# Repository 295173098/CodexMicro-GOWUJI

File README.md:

# GOWUJI Macro Pad

<p align="center"><sub><b>Rev C 工程样机</b> · 带壳 3D 渲染（CAD 渲染，非实物照片）</sub></p>

| **PCB 正面** · 4 层 · 95 × 98 mm | **PCB 背面** · 电源与地平面 |
| :---: | :---: |
|  |  |

> **当前工程候选：Rev C（REVIEW ONLY）**。四层板、直接贴装 ESP32-S3、独立 LED 5 V 阻尼支路；ERC/DRC/一致性 0，板级仿真通过，但**尚未下单、未做实物验证**。源文件在 [hardware/rev-c/](hardware/rev-c/)，验证记录见 [AGENTS.md](AGENTS.md)；Rev B 下单说明见 [docs/rev-b-order.md](docs/rev-b-order.md)。

> **Rev B PCB + 工厂贴装打样**：使用[Rev B 下单说明](docs/rev-b-order.md)和本地 `build/rev-b-pcba.zip`；工厂 CAM/供料/旋转回签后做 3–5 套工程样机。下方 A4 的双层板和成本不能代用。

<details>
<summary>更多 3D 渲染</summary>

| 背面 | 后侧 USB-C | PCB 正上方 |
| :---: | :---: | :---: |
|  |  |  |

</details>

## Rev A4 DIY 基线

按 [OpenAI × Work Louder Codex Micro](https://openai.com/zh-Hans-CN/supply/co-lab/work-louder/) 键位设计的 DIY 控制台。采用 95 × 98 mm 双层 PCB、Waveshare ESP32-S3-Zero-M、13 个直焊 MX 轴（其中两个共用 2U 语音键帽）、六颗独立状态灯、五向摇杆、带按压旋钮和触摸片。外壳、面板、旋钮、导光件和 2U 键帽可打印。当前是 **Alpha 样机设计**，尚未做实物验证。

| 交付 | 文件 |
| --- | --- |
| PCB、原理图、项目库 | [KiCad 项目](hardware/Gowuji-RevA.kicad_pro)、[PCB](hardware/Gowuji-RevA.kicad_pcb)、[原理图](hardware/Gowuji-RevA.kicad_sch) |
| BOM | [BOM.csv](hardware/BOM.csv) |
| 3D 打印 | [底壳](mechanical/base.stl)、[面板](mechanical/plate.stl)、[旋钮](mechanical/dial.stl)、[摇杆帽](mechanical/joystick-cap.stl)、[导光件](mechanical/light-pipes.stl)、[2U 语音键帽](mechanical/ptt-keycap-2u.stl)、[USB 盖](mechanical/usb-cover.stl)、[轴孔试片](mechanical/mx-fit-coupon.stl)、[装配 STEP](mechanical/fit-reference.step) |
| 可选外壳 | [按参考图制作的凹刻圆盘和正面选件](docs/appearance.md) |
| Rev B 布线已闭合，待打样验证 | [直接贴装 ESP32-S3、后置 USB-C 和连续正面](docs/rev-b.md) |
| 固件和烧录 | [Arduino 工程](firmware/Gowuji/)、[烧录脚本](firmware/flash.py) |
| Codex 伴侣 | [Python 主机程序](host/gowuji.py) |
| 制造与验证 | [打样和装配](docs/assembly.md)、[验证记录](docs/validation.md) |

有线模式使用标准 USB HID 键盘；打开伴侣应用并连接 USB 串口后，按键事件改由伴侣处理。按住旋钮再按复位，选择本次开机使用 BLE HID。无线模式需要通过 USB-C 外接 5 V 电源；Rev A 无电池、充电器和无线状态灯同步。普通开机恢复 USB HID。蓝牙配对和 USB 真机枚举尚未验证。

伴侣应用启动独立的 [Codex App Server](https://learn.chatgpt.com/docs/app-server)，不用原厂 VID/PID 或专有协议。它管理自己启动或接入的聊天；不能保证追踪官方桌面应用里正在运行的聊天，也不会出现在原厂设备配置页。旋钮选择下一次发送使用的推理强度，摇杆把提示词填入输入框。A4 的板载数字麦克风通过 USB 传送 16 kHz 单声道 PCM 给伴侣，由本地 Vosk 转写。按住 2U 键采样，松开停止，每次最多 60 秒；系统录音应用和 BLE 模式不提供板载音频。语音和摇杆都只填入草稿，由用户点发送。按键接受/拒绝只对当前会话中已经显示的命令或文件审批有效。

PCB 上六颗灯靠近上方六个磨砂透光状态键，通过面板导光；六个位置映射到伴侣的聊天槽。状态为：无分配熄灭、空闲白、运行蓝、完成绿、待输入黄、错误红。左下触摸片切换六个配置层；底部宽键下两轴合并为一个按住说话事件。传入 `--profiles host/profiles.example.json` 可替换每层的摇杆提示词和部分命令键；标准 HID 模式保持固定键值。

| 位置 | 第 1 列 | 第 2 列 | 第 3 列 | 第 4 列 |
| --- | --- | --- | --- | --- |
| 第 1 排 | 旋钮 | 会话 1 | 会话 2 | 摇杆 |
| 第 2 排 | 会话 3 | 会话 4 | 会话 5 | 会话 6 |
| 第 3 排 | 新聊天 | 接受 | 拒绝 | 中止当前回合 |
| 第 4 排 | 触摸切层 | 按住说话（2U 左） | 同一键（2U 右） | 查找 / 分配 |

成本估算约 **¥63–170 / 套**，含小批量摊销裸 PCB 和自打耗材，不含人工、运费、代贴和外置电源。板载麦克风、阻容和密封圈约增加 ¥3–10。六个状态位用磨砂透光 1U MX 键帽，其余单宽命令键可复用通用键帽。量产前必须完成 [USB 与整机首件验证](docs/validation.md)。

本地编译和启动：

```powershell
python tools/build_firmware.py --install
python -m pip install esptool==5.1.0
python firmware/flash.py COM6 GOWUJI-v0.1.0-alpha.4-flash-0x0.bin
python -m pip install -r host/requirements.txt
python host/gowuji.py --port COM6 --cwd C:/path/to/project
```

上面用的是 Windows 示例端口；macOS/Linux 替换成对应串口路径。无需硬件可用 `python host/gowuji.py --demo` 查看灯状态。语音可选装 `host/requirements-voice.txt`，下载匹配语言的 [Vosk 模型](https://alphacephei.com/vosk/models)，并启动时增加 `--voice-model <模型目录>`。若使用 A3 或希望改用电脑麦克风，另装 `sounddevice`，并增加 `--mic computer`。

硬件使用 KiCad 9 打开。修改源数据后可用 `python tools/hardware.py` 更新原理图、BOM、项目库及固件引脚；该命令不会覆写已布线 PCB。若重新布局，`--unrouted build/layout.kicad_pcb` 生成裸布局，再在 KiCad 中布线并另存。用 `python mechanical/generate.py`（CadQuery 2.8）重建机械文件。用 `python tools/export_hardware.py` 重跑检查和制造导出。Release 同时提供可烧录的完整镜像、源码和 Gerber，发布状态见 [AGENTS.md](AGENTS.md)。

在 PCB 编辑器按 `Alt+3` 查看装有器件的板。`hardware/models/` 内含简化的按键、模块、旋钮、摇杆和麦克风 STEP，可用 `python mechanical/kicad_models.py` 重建。`python tools/export_hardware.py --render` 额外生成电路板和带外壳两张 KiCad 渲染图。A4 延用 A3 对齐原厂的键位及按键分区，采用通用 MX 轴、打印外壳和独立伴侣程序；命令默认映射、手感、材料及灯光效果与原厂可能不同。

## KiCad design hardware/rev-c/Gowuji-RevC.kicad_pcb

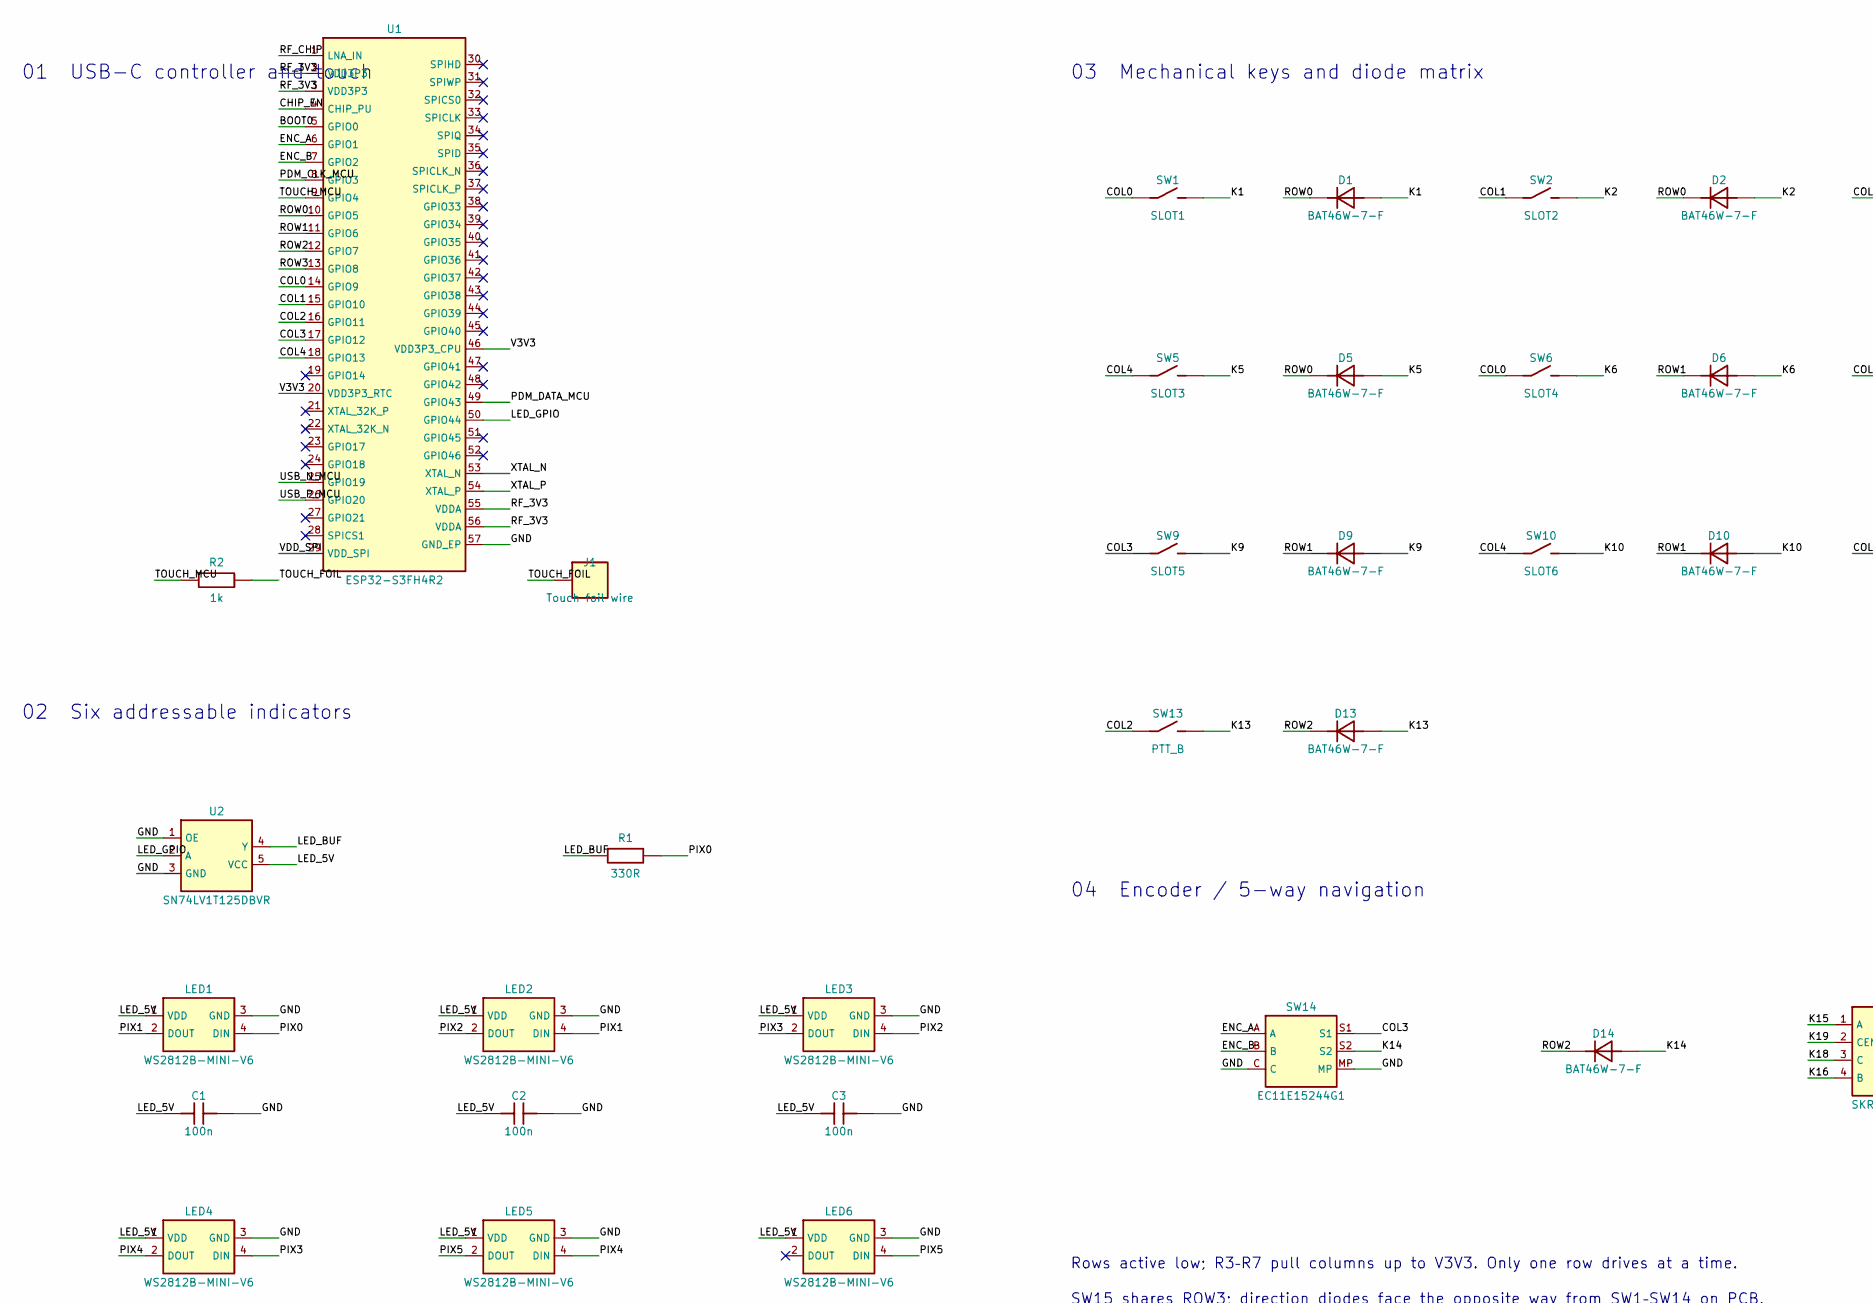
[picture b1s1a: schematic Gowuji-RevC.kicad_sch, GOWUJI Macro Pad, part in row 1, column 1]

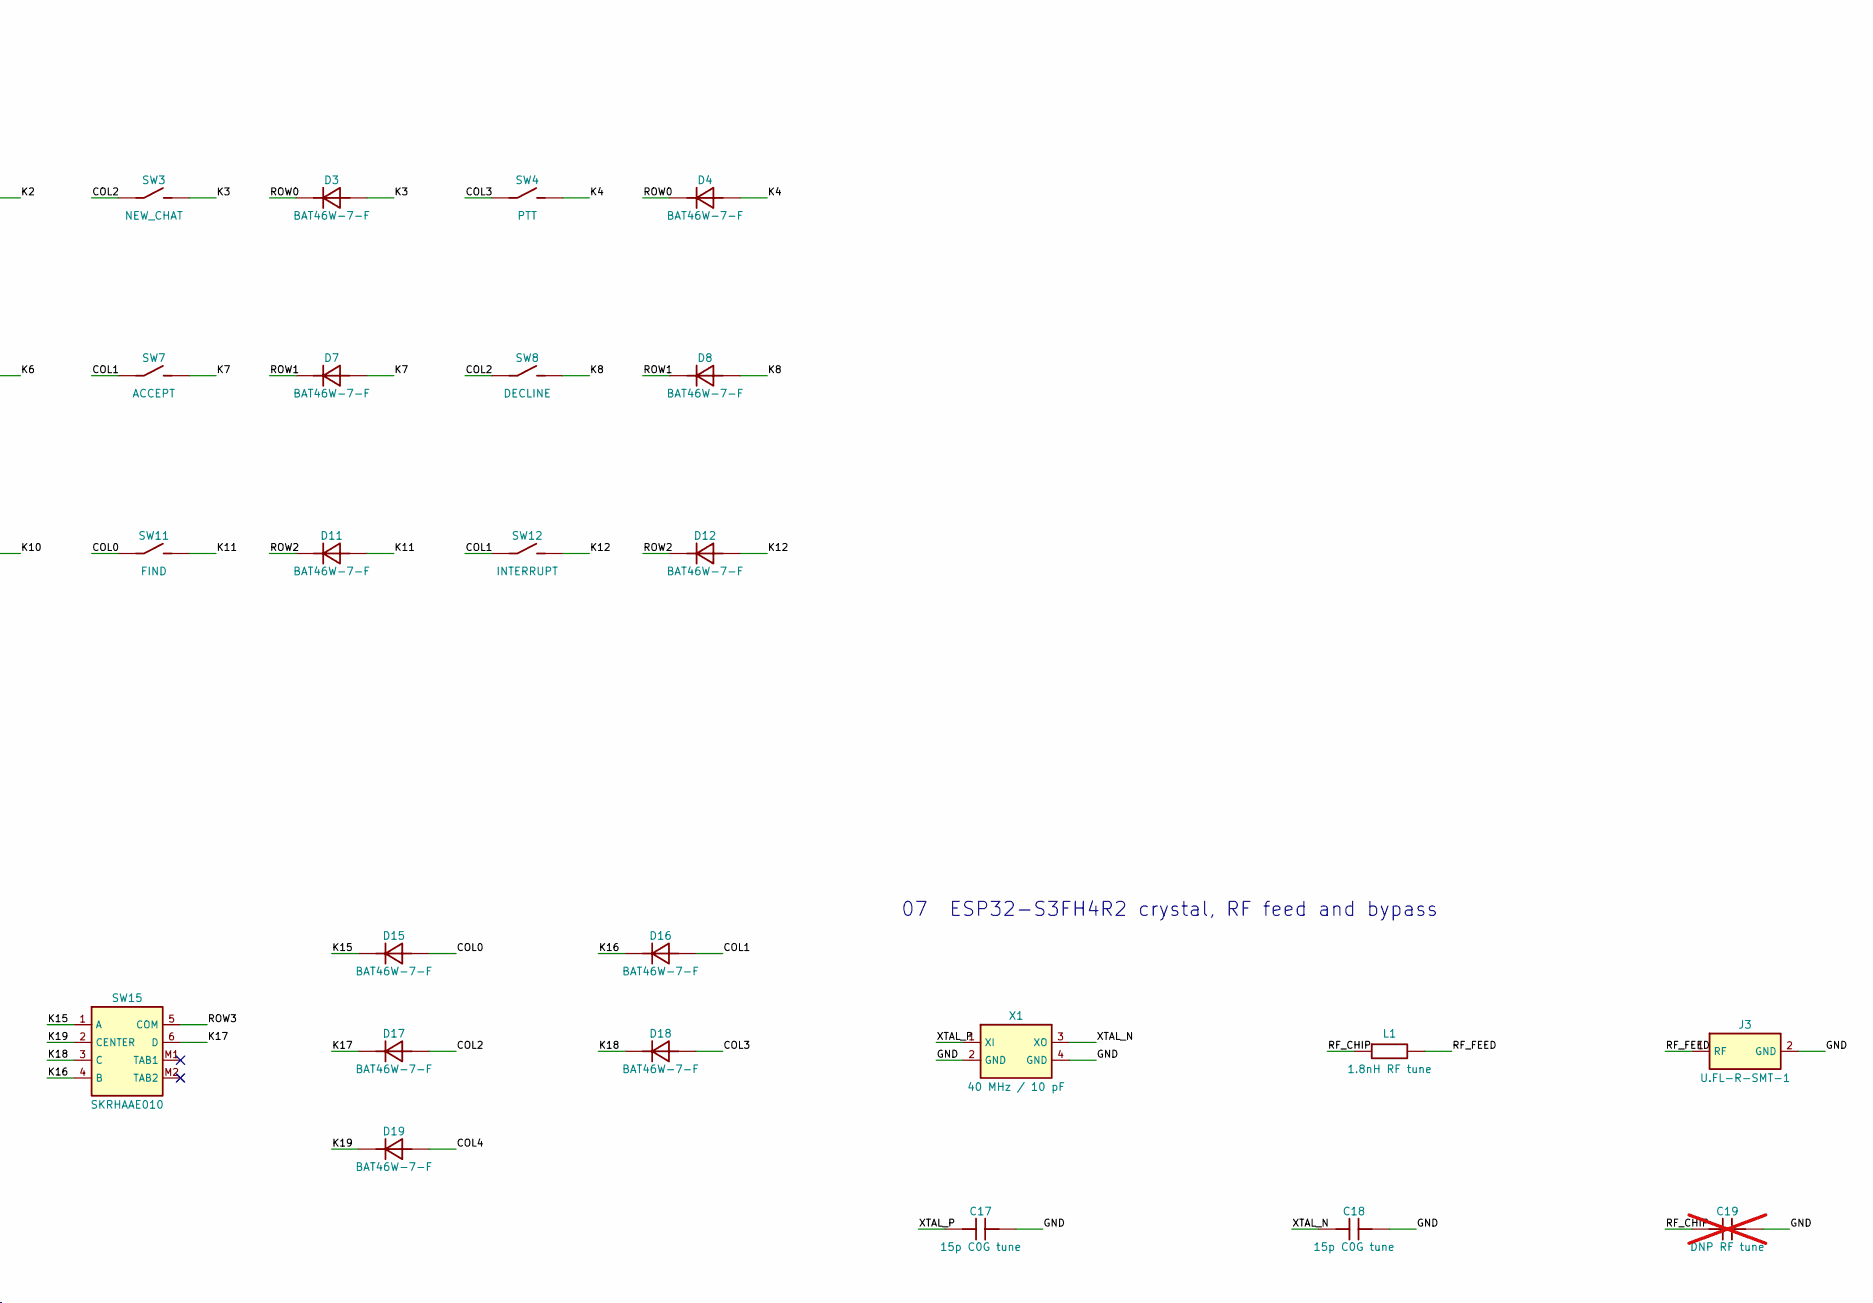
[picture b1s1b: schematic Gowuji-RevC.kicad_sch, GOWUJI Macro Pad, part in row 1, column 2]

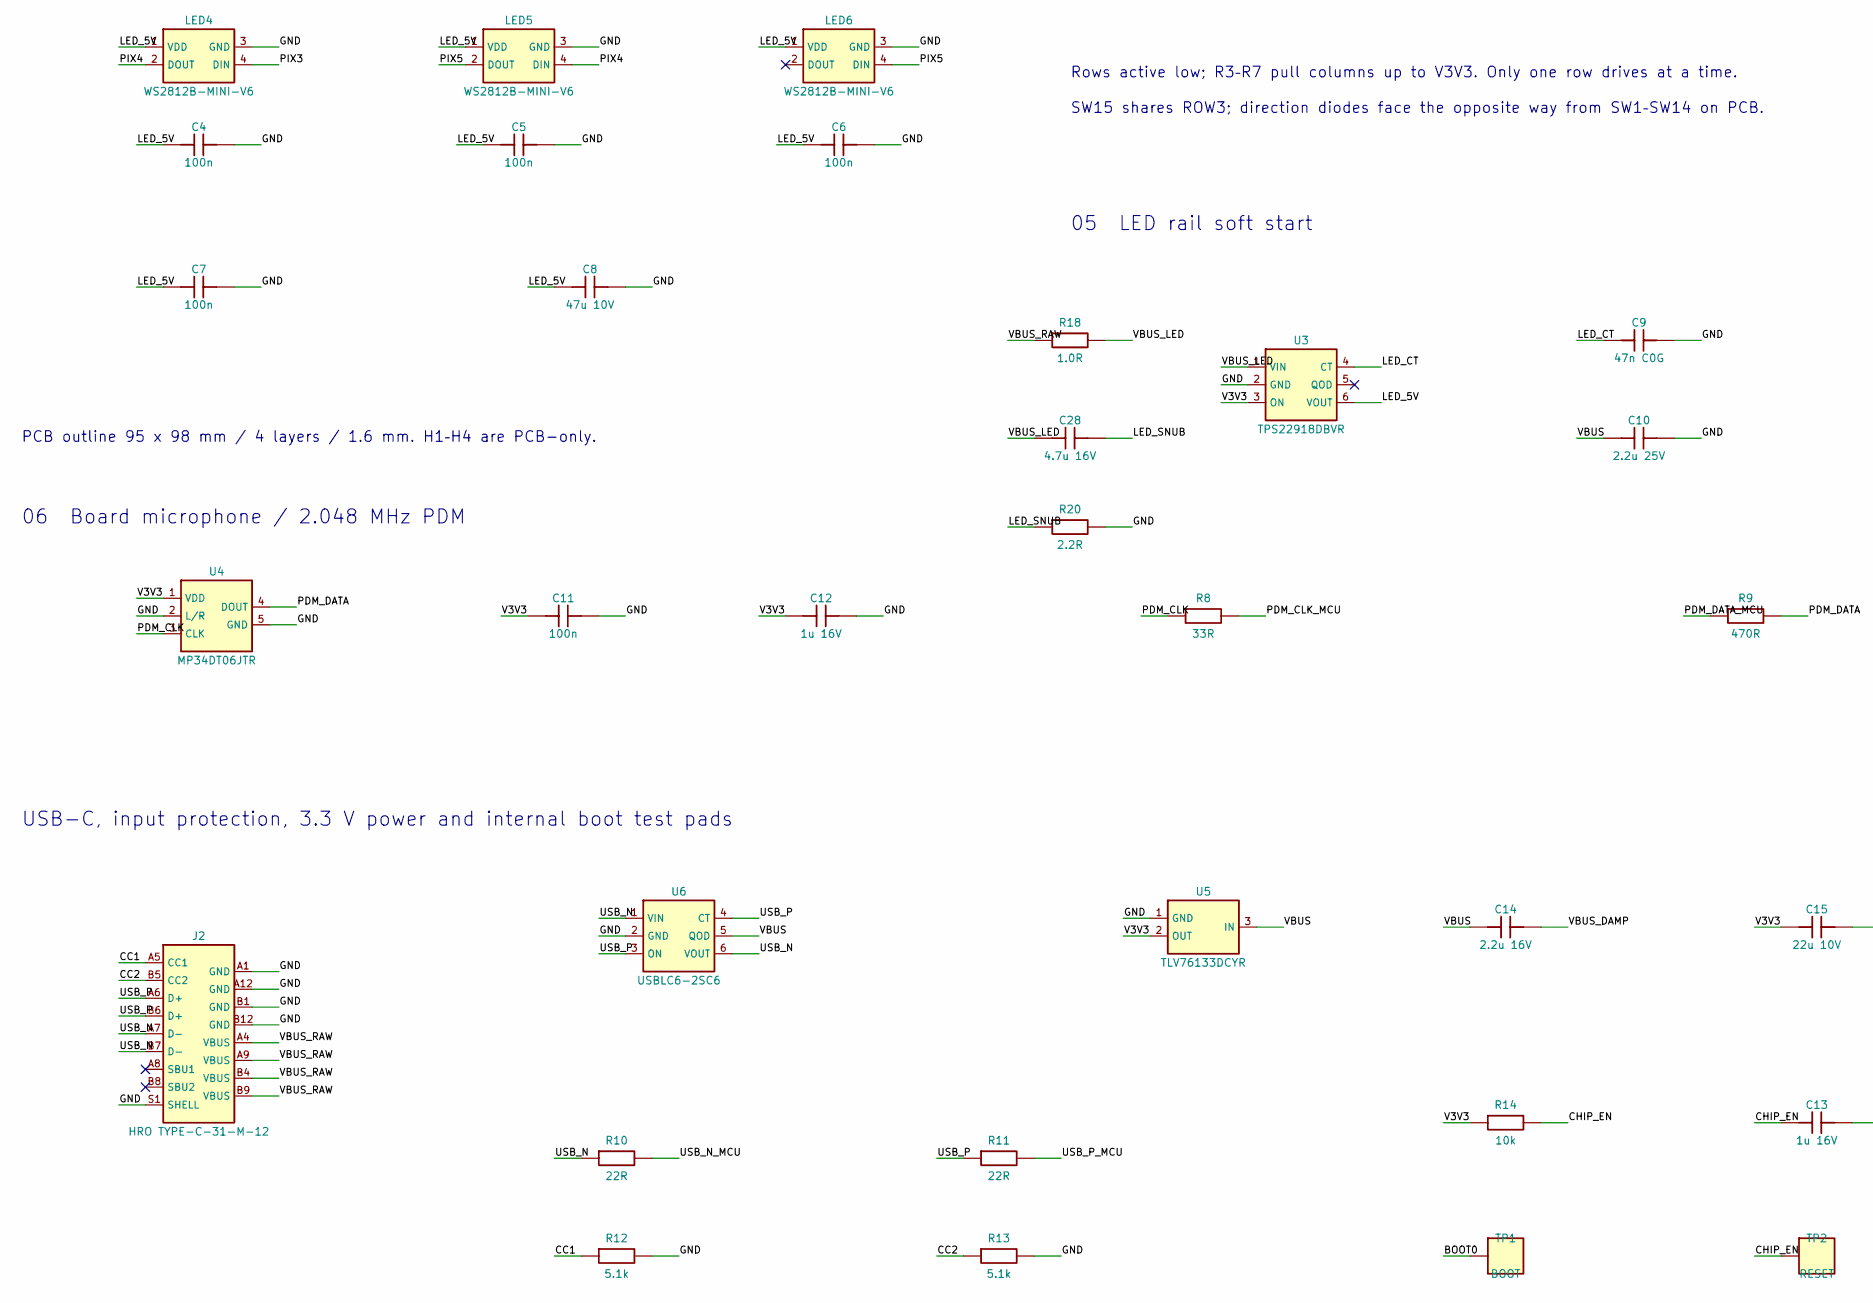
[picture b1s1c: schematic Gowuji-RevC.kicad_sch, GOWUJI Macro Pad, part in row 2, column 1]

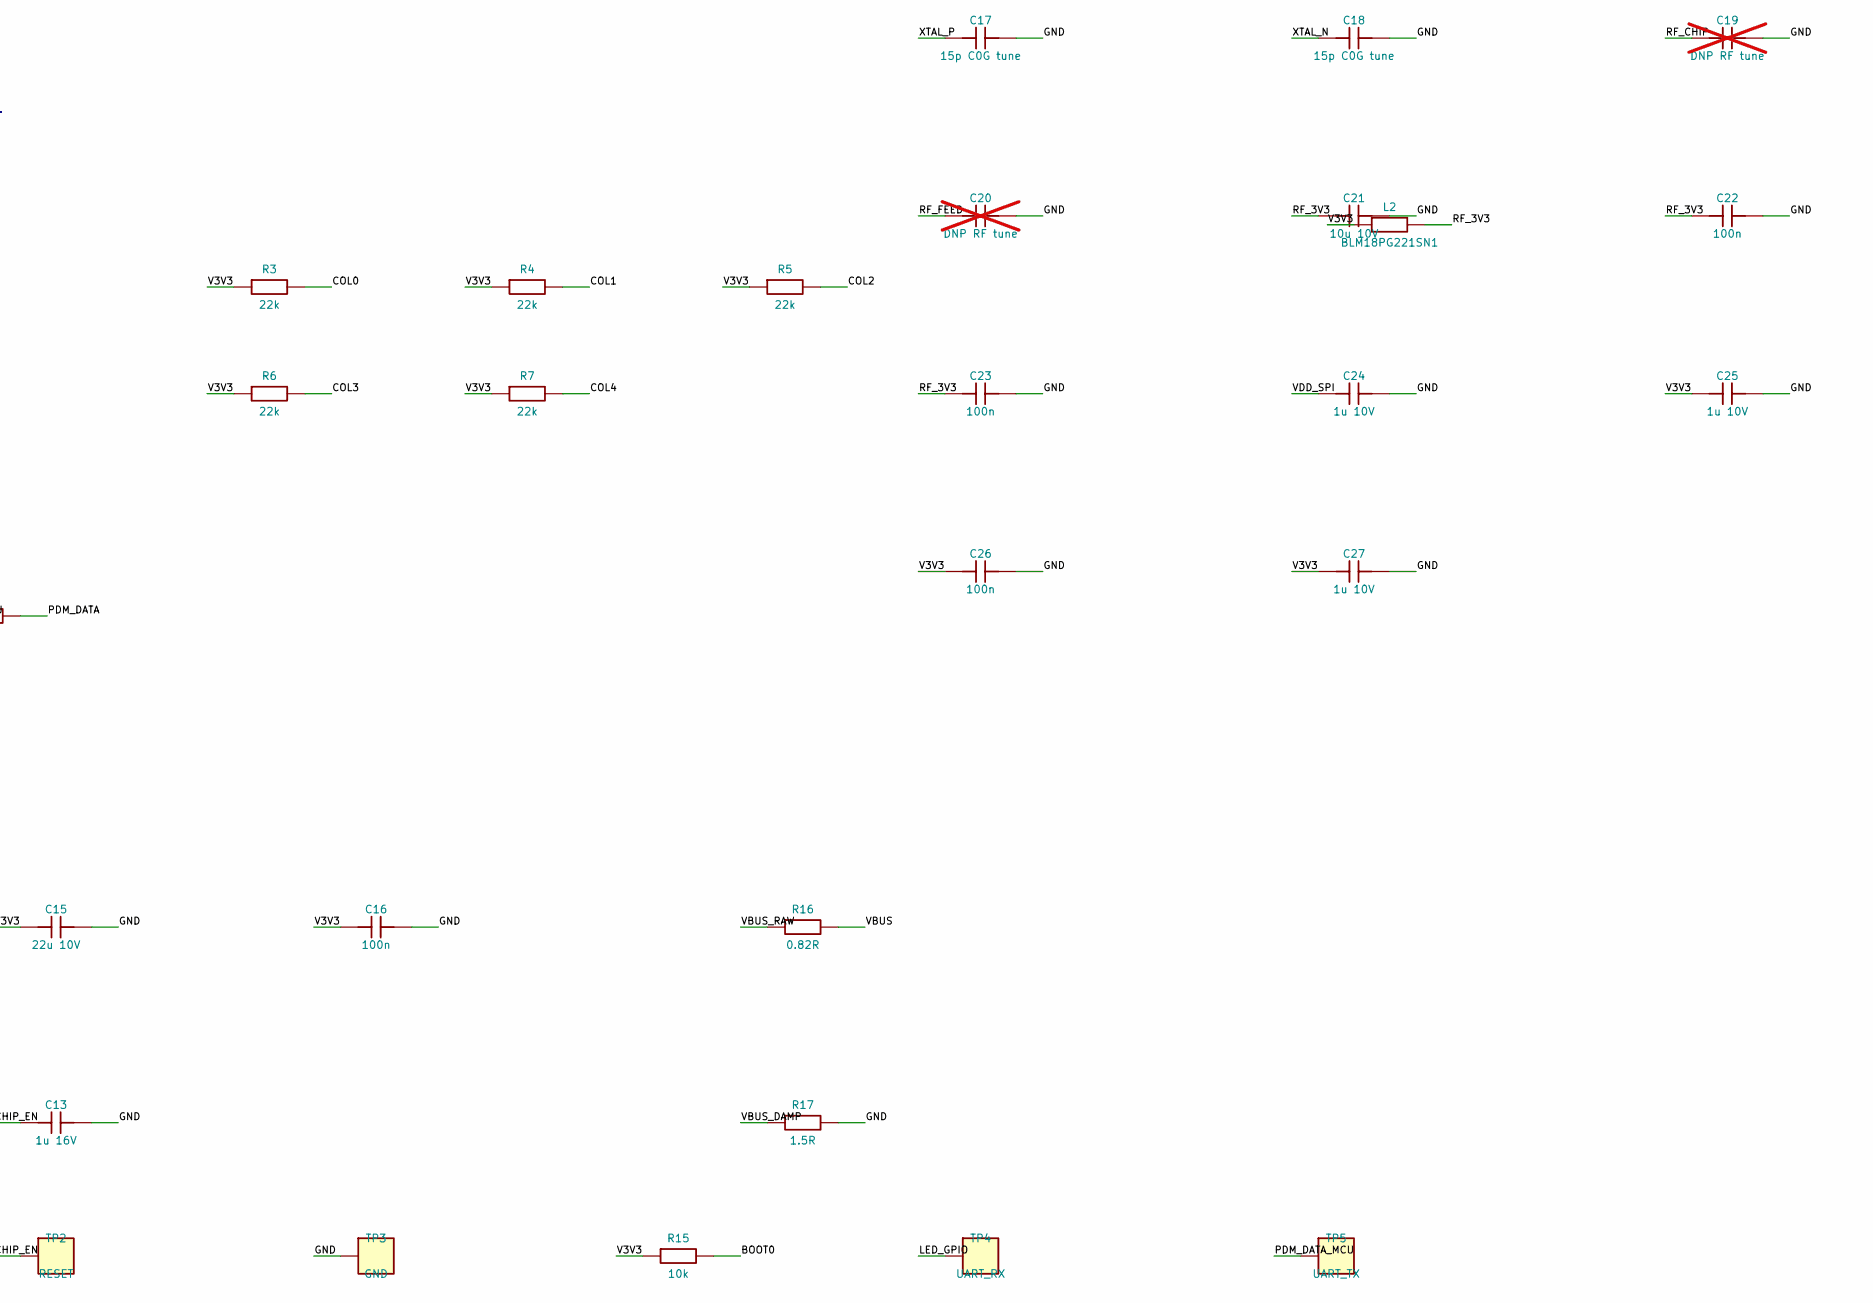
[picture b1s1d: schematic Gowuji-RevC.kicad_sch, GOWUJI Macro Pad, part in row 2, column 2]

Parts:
C1, C2, C3, C4, C5, C6, C7, C11, C16, C22, C23, C26: 100n; C0603
C8: 47u 10V; C1206
C9: 47n C0G; C0603
C10: 2.2u 25V; C0603
C12, C13: 1u 16V; C0603
C14: 2.2u 16V; C1206
C15: 22u 10V; C1206
C17, C18: 15p C0G tune; C0603
C19, C20: DNP RF tune; C0603; not fitted
C21: 10u 10V; C0603
C24, C25, C27: 1u 10V; C0603
C28: 4.7u 16V; C1206
D1, D2, D3, D4, D5, D6, D7, D8, D9, D10, D11, D12, D13, D14, D15, D16, D17, D18, D19: BAT46W-7-F; SOD123
J1: Touch foil wire; Wire
J2: HRO TYPE-C-31-M-12; USB_C
J3: U.FL-R-SMT-1; U.FL_Hirose_U.FL-R-SMT-1_Vertical
L1: 1.8nH RF tune; R0603
L2: BLM18PG221SN1; R0603
LED1, LED2, LED3, LED4, LED5, LED6: WS2812B-MINI-V6; RGB3535
R1: 330R; R0603
R2: 1k; R0603
R3, R4, R5, R6, R7: 22k; R0603
R8: 33R; R0603
R9: 470R; R0603
R10, R11: 22R; R0603
R12, R13: 5.1k; R0603
R14, R15: 10k; R0603
R16: 0.82R; R_1206_3216Metric
R17: 1.5R; R0603
R18: 1.0R; R_1206_3216Metric
R20: 2.2R; R_1206_3216Metric
SW1: SLOT1; MX
SW2: SLOT2; MX
SW3: NEW_CHAT; MX
SW4: PTT; MX
SW5: SLOT3; MX
SW6: SLOT4; MX
SW7: ACCEPT; MX
SW8: DECLINE; MX
SW9: SLOT5; MX
SW10: SLOT6; MX
SW11: FIND; MX
SW12: INTERRUPT; MX
SW13: PTT_B; MX
SW14: EC11E15244G1; EC11
SW15: SKRHAAE010; SKRH
TP1: BOOT; Probe
TP2: RESET; Probe
TP3: GND; Probe
TP4: UART_RX; Probe
TP5: UART_TX; Probe
U1: ESP32-S3FH4R2; S3
U2: SN74LV1T125DBVR; SOT23_5
U3: TPS22918DBVR; SOT23_6
U4: MP34DT06JTR; MP34DT06J
U5: TLV76133DCYR; LDO
U6: USBLC6-2SC6; SOT23_6
X1: 40 MHz / 10 pF; Crystal_SMD_3225-4Pin_3.2x2.5mm

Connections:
/BOOT0: R15.2, TP1.1, U1.5 (GPIO0)
/CC1: J2.A5 (CC1), R12.1
/CC2: J2.B5 (CC2), R13.1
/CHIP_EN: C13.1, R14.2, TP2.1, U1.4 (CHIP_PU)
/COL0: D15.2 (A), R3.2, SW1.1, SW6.1, SW11.1, U1.14 (GPIO9)
/COL1: D16.2 (A), R4.2, SW2.1, SW7.1, SW12.1, U1.15 (GPIO10)
/COL2: D17.2 (A), R5.2, SW3.1, SW8.1, SW13.1, U1.16 (GPIO11)
/COL3: D18.2 (A), R6.2, SW4.1, SW9.1, SW14.S1, U1.17 (GPIO12)
/COL4: D19.2 (A), R7.2, SW5.1, SW10.1, U1.18 (GPIO13)
/ENC_A: SW14.A, U1.6 (GPIO1)
/ENC_B: SW14.B, U1.7 (GPIO2)
/GND: C1.2, C2.2, C3.2, C4.2, C5.2, C6.2, C7.2, C8.2, C9.2, C10.2, C11.2, C12.2, C13.2, C15.2, C16.2, C17.2, C18.2, C19.2, C20.2, C21.2, C22.2, C23.2, C24.2, C25.2, C26.2, C27.2, J2.A1 (GND), J2.A12 (GND), J2.B1 (GND), J2.B12 (GND), J2.S1 (SHELL), J3.2 (GND), LED1.3 (GND), LED2.3 (GND), LED3.3 (GND), LED4.3 (GND), LED5.3 (GND), LED6.3 (GND), R12.2, R13.2, R17.2, R20.2, SW14.C, SW14.MP, TP3.1, U1.57 (GND_EP), U2.1 (OE), U2.3 (GND), U3.2 (GND), U4.2 (L/R), U4.5 (GND), U5.1 (GND), U6.2 (GND), X1.2 (GND), X1.4 (GND)
/K1: D1.2 (A), SW1.2
/K2: D2.2 (A), SW2.2
/K3: D3.2 (A), SW3.2
/K4: D4.2 (A), SW4.2
/K5: D5.2 (A), SW5.2
/K6: D6.2 (A), SW6.2
/K7: D7.2 (A), SW7.2
/K8: D8.2 (A), SW8.2
/K9: D9.2 (A), SW9.2
/K10: D10.2 (A), SW10.2
/K11: D11.2 (A), SW11.2
/K12: D12.2 (A), SW12.2
/K13: D13.2 (A), SW13.2
/K14: D14.2 (A), SW14.S2
/K15: D15.1 (K), SW15.1 (A)
/K16: D16.1 (K), SW15.4 (B)
/K17: D17.1 (K), SW15.6 (D)
/K18: D18.1 (K), SW15.3 (C)
/K19: D19.1 (K), SW15.2 (CENTER)
/LED_5V: C1.1, C2.1, C3.1, C4.1, C5.1, C6.1, C7.1, C8.1, LED1.1 (VDD), LED2.1 (VDD), LED3.1 (VDD), LED4.1 (VDD), LED5.1 (VDD), LED6.1 (VDD), U2.5 (VCC), U3.6 (VOUT)
/LED_BUF: R1.1, U2.4 (Y)
/LED_CT: C9.1, U3.4 (CT)
/LED_GPIO: TP4.1, U1.50 (GPIO44), U2.2 (A)
/LED_SNUB: C28.2, R20.1
/PDM_CLK: R8.1, U4.3 (CLK)
/PDM_CLK_MCU: R8.2, U1.8 (GPIO3)
/PDM_DATA: R9.2, U4.4 (DOUT)
/PDM_DATA_MCU: R9.1, TP5.1, U1.49 (GPIO43)
/PIX0: LED1.4 (DIN), R1.2
/PIX1: LED1.2 (DOUT), LED2.4 (DIN)
/PIX2: LED2.2 (DOUT), LED3.4 (DIN)
/PIX3: LED3.2 (DOUT), LED4.4 (DIN)
/PIX4: LED4.2 (DOUT), LED5.4 (DIN)
/PIX5: LED5.2 (DOUT), LED6.4 (DIN)
/RF_3V3: C21.1, C22.1, C23.1, L2.2, U1.2 (VDD3P3), U1.3 (VDD3P3), U1.55 (VDDA), U1.56 (VDDA)
/RF_CHIP: C19.1, L1.1, U1.1 (LNA_IN)
/RF_FEED: C20.1, J3.1 (RF), L1.2
/ROW0: D1.1 (K), D2.1 (K), D3.1 (K), D4.1 (K), D5.1 (K), U1.10 (GPIO5)
/ROW1: D6.1 (K), D7.1 (K), D8.1 (K), D9.1 (K), D10.1 (K), U1.11 (GPIO6)
/ROW2: D11.1 (K), D12.1 (K), D13.1 (K), D14.1 (K), U1.12 (GPIO7)
/ROW3: SW15.5 (COM), U1.13 (GPIO8)
/TOUCH_FOIL: J1.1, R2.2
/TOUCH_MCU: R2.1, U1.9 (GPIO4)
/USB_N: J2.A7 (D-), J2.B7 (D-), R10.1, U6.1 (VIN), U6.6 (VOUT)
/USB_N_MCU: R10.2, U1.25 (GPIO19)
/USB_P: J2.A6 (D+), J2.B6 (D+), R11.1, U6.3 (ON), U6.4 (CT)
/USB_P_MCU: R11.2, U1.26 (GPIO20)
/V3V3: C11.1, C12.1, C15.1, C16.1, C25.1, C26.1, C27.1, L2.1, R3.1, R4.1, R5.1, R6.1, R7.1, R14.1, R15.1, U1.20 (VDD3P3_RTC), U1.46 (VDD3P3_CPU), U3.3 (ON), U4.1 (VDD), U5.2 (OUT)
/VBUS: C10.1, C14.1, R16.2, U5.3 (IN), U6.5 (QOD)
/VBUS_DAMP: C14.2, R17.1
/VBUS_LED: C28.1, R18.2, U3.1 (VIN)
/VBUS_RAW: J2.A4 (VBUS), J2.A9 (VBUS), J2.B4 (VBUS), J2.B9 (VBUS), R16.1, R18.1
/VDD_SPI: C24.1, U1.29 (VDD_SPI)
/XTAL_N: C18.1, U1.53 (XTAL_N), X1.3 (XO)
/XTAL_P: C17.1, U1.54 (XTAL_P), X1.1 (XI)

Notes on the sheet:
01 USB-C controller and touch
02 Six addressable indicators
05 LED rail soft start
03 Mechanical keys and diode matrix
04 Encoder / 5-way navigation
Rows active low; R3–R7 pull columns up to V3V3. Only one row drives at a time.
USB-C, input protection, 3.3 V power and internal boot test pads
07 ESP32-S3FH4R2 crystal, RF feed and bypass
SW15 shares ROW3; direction diodes face the opposite way from SW1–SW14 on PCB.
PCB outline 95 x 98 mm / 4 layers / 1.6 mm. H1–H4 are PCB-only.
06 Board microphone / 2.048 MHz PDM

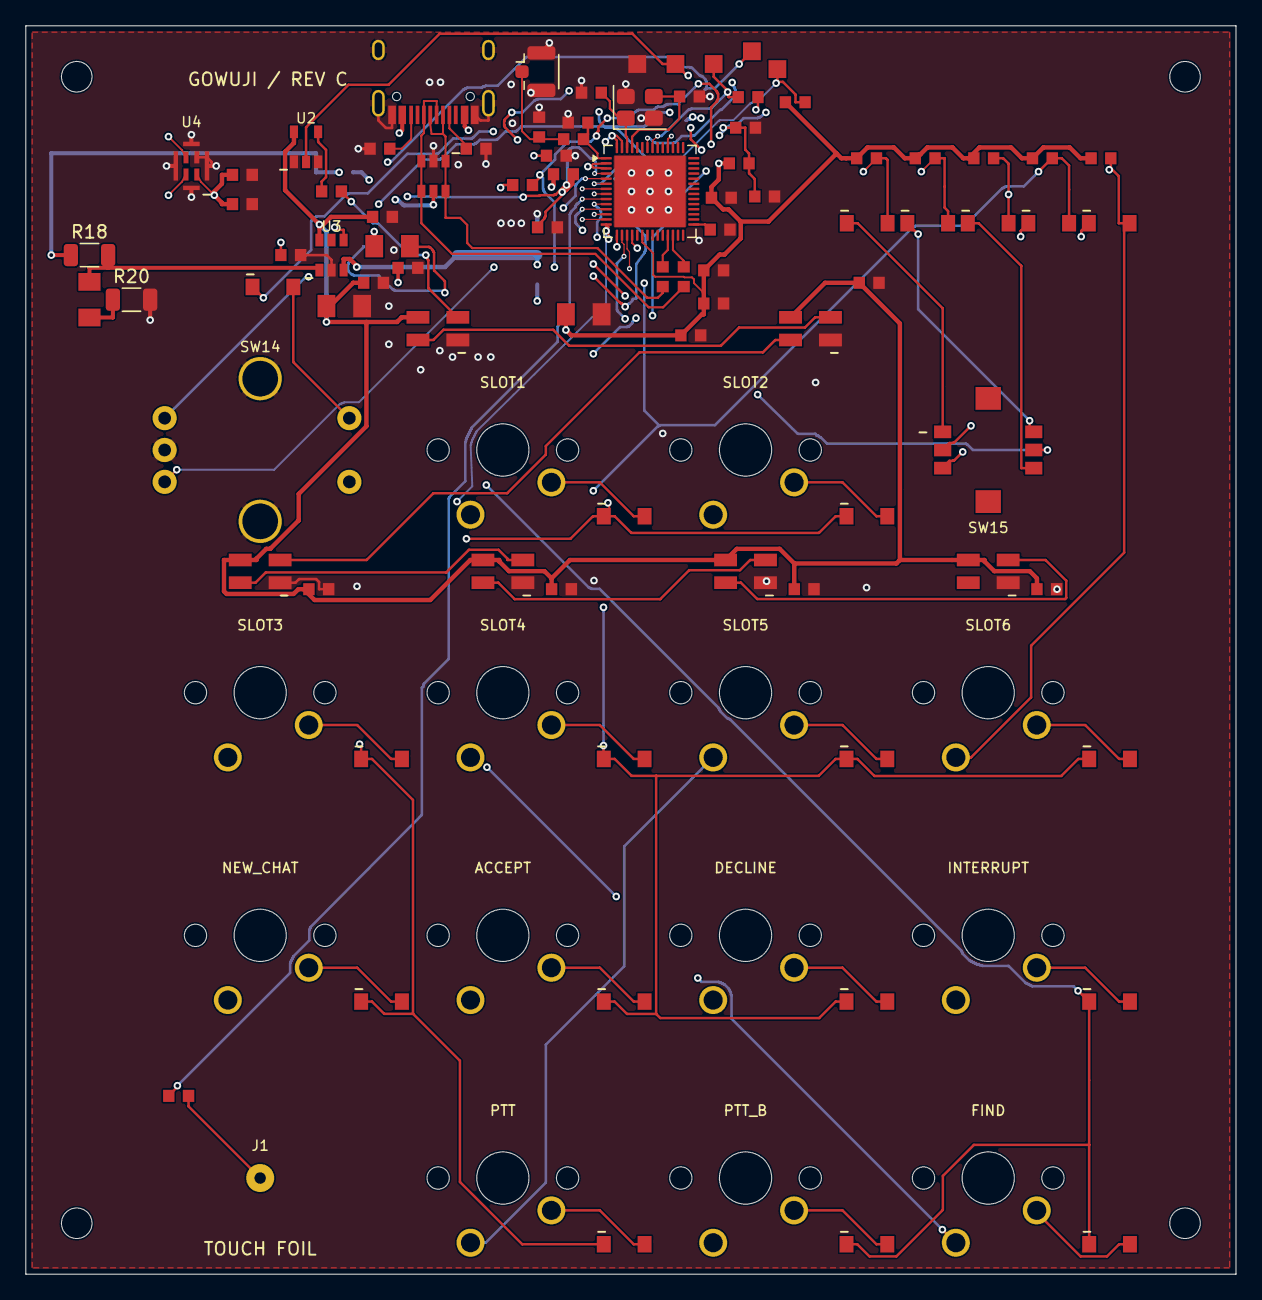
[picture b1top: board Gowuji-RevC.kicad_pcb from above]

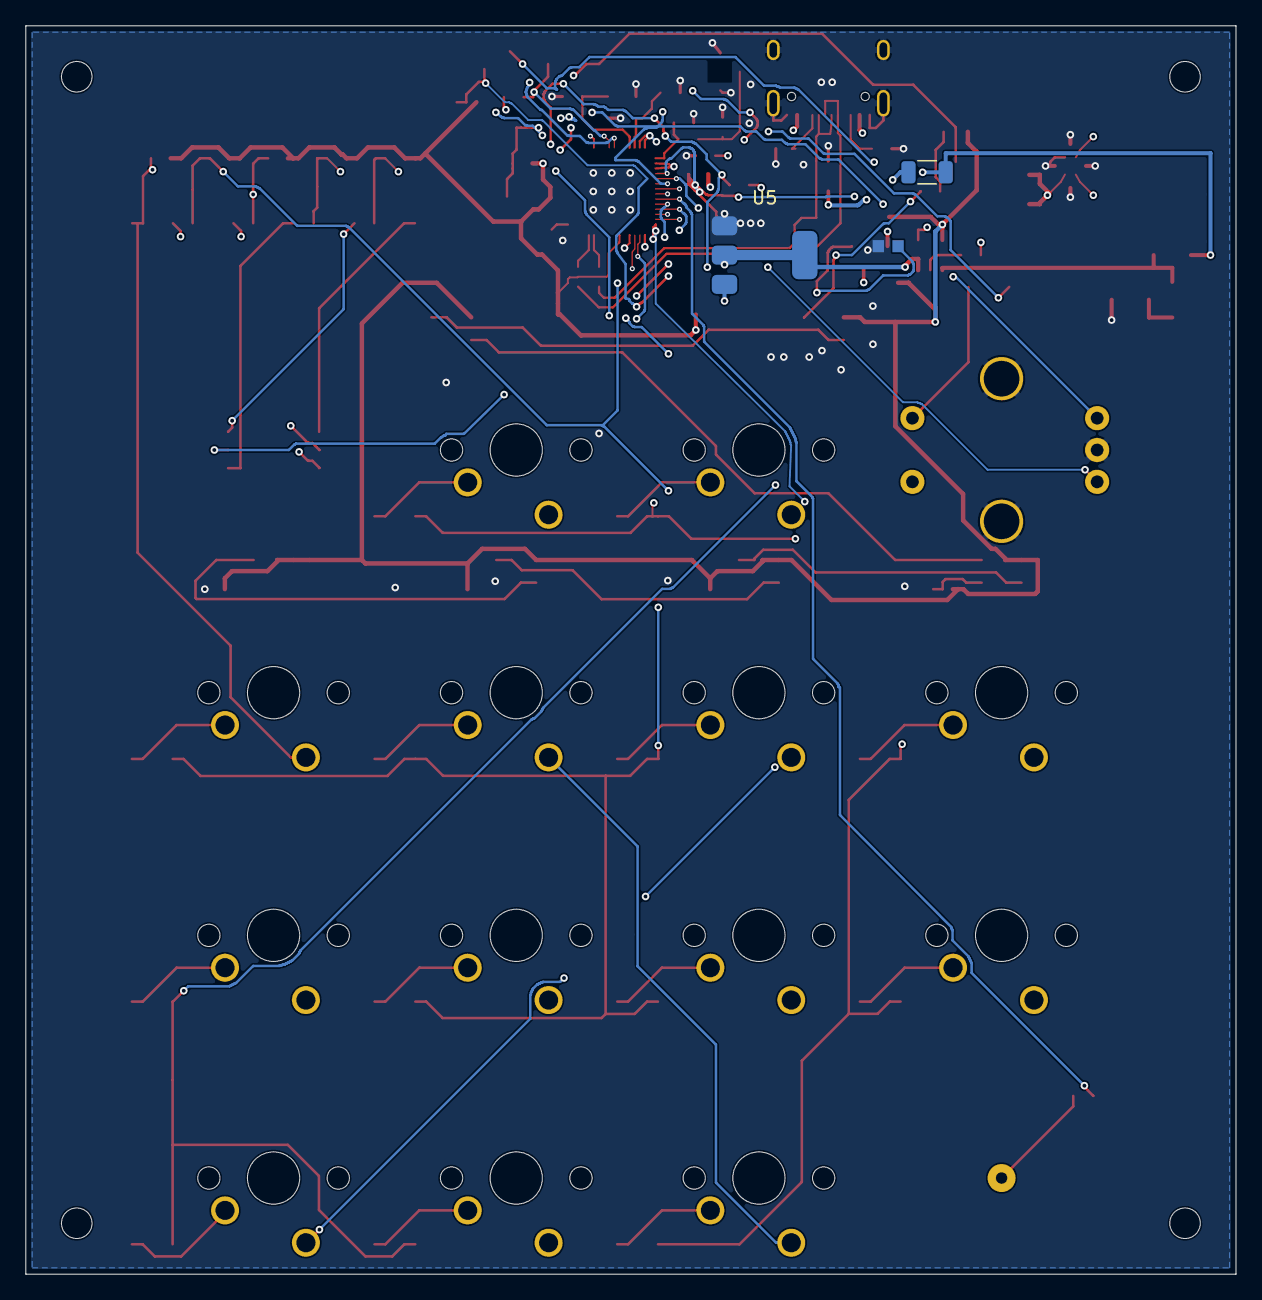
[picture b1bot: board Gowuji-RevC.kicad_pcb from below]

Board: 4 copper layers, 95.0 x 98.0 mm, 108 parts (3 on the bottom side), 67 nets.

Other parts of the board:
H1, H2, H3, H4: M2; Mount

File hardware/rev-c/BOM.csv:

Refs,Qty,Part,Notes,CNY low,CNY high
U2,1,TI SN74LV1T125DBVR,SOT-23-5; 1.8–5.5 V translator,0.7,2.5
U3,1,TI TPS22918DBVR,SOT-23-6; 5 V LED rail load switch,1.5,5
SW1-SW13,13,MX-compatible 3-pin or 5-pin switches,solder type; match SW4 and SW13 for the shared 2U cap,0.65,1.5
SW14,1,ALPS EC11E15244G1,push encoder; confirm drawing / D shaft,5,12
SW15,1,ALPS SKRHAAE010,no guide bosses; verify footprint before substituting,5,16
D1-D19,19,Diodes Inc. BAT46W-7-F,SOD-123; low forward drop Schottky,0.08,0.3
LED1-LED6,6,Worldsemi WS2812B-MINI-V6,3535; verify MINI-V6 (no X1 suffix),0.3,0.9
R1,1,330 ohm,0603,0.02,0.1
R2,1,1 kohm,0603,0.02,0.1
R3-R7,5,22 kohm ±1%,0603; matrix column pull-ups,0.02,0.1
C1-C7,7,100 nF X7R 16 V,0603,0.04,0.12
C8,1,47 uF X5R 10 V,1206; ceramic,0.3,1
C9,1,47 nF C0G 50 V,0603; load-switch slew-rate capacitor; ~129 ms 10-90% at 5 V,0.06,0.25
U4,1,ST MP34DT06JTR,C503097; top-port PDM; no wash or coating over inlet,3,9
C11,1,100 nF X7R 16 V,0603; microphone bypass,0.04,0.12
C12,1,1 uF X7R 16 V,0603; microphone bypass,0.05,0.2
R8,1,33 ohm,0603; source series resistor on PDM clock,0.02,0.1
R9,1,470 ohm,0603; limits contention at GPIO43 during reset,0.02,0.1
MIC-SEAL,1,"0.8 mm closed-cell foam, ID 1.6 mm / OD 2.8 mm",ring on underside of plate; keep inlet clear,0.1,0.5
CAPS-A,6,MX 1U frosted translucent keycaps,matte clear or milky PC; 17.9 mm reference width,0.7,2.5
CAPS-C,5,MX 1U opaque command caps,add optional icon decals,0.35,1.2
PRINT,1,PLA/PETG + translucent material,"base, plate, knobs, light pipes and dual-stem 2U cap",4.5,11
SCREWS,4,M2x10 pan-head screws,self-tap into printed pilot holes,0.1,0.35
FOIL,1,Copper adhesive foil + thin wire,14 mm square + 50 mm wire,0.2,1
USB,1,USB-C data cable,reuse an existing cable,0,8
PCB,1,4-layer FR4 1.6 mm,95 x 98 mm; quote exact controlled impedance stackup,,
U1,1,ESP32-S3FH4R2,"QFN56, 4 MB QSPI flash, 2 MB PSRAM",,
J2,1,HRO TYPE-C-31-M-12,USB 2.0 16-pin; shell soldered,0.8,2.8
U5,1,TLV76133DCYR,3.3 V 1 A LDO; SOT-223; verify temperature,1.8,4.5
U6,1,USBLC6-2SC6,USB data ESD; SOT-23-6,0.35,1.5
R10-R11,2,22 ohm,0603 USB source damping,0.02,0.1
R12-R13,2,5.1 kohm 1%,0603 Type-C sink Rd,0.02,0.1
R14,1,10 kohm,0603 enable pull-up,0.02,0.1
C13,1,1 uF 16 V X7R,0603 enable delay,0.05,0.2
C10,1,2.2 uF 25 V X7R,0603 direct VBUS bypass; >=1 uF effective at 5.25 V including tolerance,,
C14,1,2.2 uF 16 V X7R,"1206 VBUS damping branch, paired with R17; reduced from 4.7 uF to hold hot-plug charge",0.08,0.3
R16,1,0.82 ohm 5% 0.5 W,1206 pulse-rated; check hot-plug waveform (4.50 A peak and 64.7 uJ maximum in separate model cases),,
R17,1,1.5 ohm 5%,0603 VBUS damping branch; check pulse curve,,
R18,1,1.0 ohm 1% 0.5 W,1206 pulse-rated LED branch series resistor; check hot-plug pulse,0.15,0.6
C28,1,4.7 uF 16 V X7R,1206 VBUS_LED branch damping capacitor; paired with R20,0.1,0.35
R20,1,2.2 ohm 1% 0.5 W,1206 pulse-rated LED input snubber; check hot-plug pulse,0.15,0.6
C15,1,22 uF 10 V X7R,"1206 3.3 V bulk, check DC bias",0.2,0.8
C16,1,100 nF 16 V X7R,0603 module bypass,0.04,0.12
X1,1,40 MHz 3225 4-pin crystal,10 pF CL; confirm exact part and trim,,
L1,1,1.8 nH RF inductor,starting value; tune with VNA,,
L2,1,Murata BLM18PG221SN1,RF supply ferrite,,
C17-C18,2,15 pF C0G,starting crystal load values; trim,,
C19-C20,0,RF matching positions,DNP until tuned,0,0
C21,1,10 uF 10 V,RF rail bulk,,
"C22-C23,C26",3,100 nF,supply bypass,,
"C24-C25,C27",3,1 uF 10 V,supply bypass,,
R15,1,10 kohm,BOOT pull-up,,
J3,1,Hirose U.FL-R-SMT-1,"50 ohm, internal antenna",,
ANT1,1,2.4 GHz 50 ohm adhesive FPC antenna,u.FL compatible; select and tune in enclosure,,
TP1-TP5,5,Bare pads,internal service,0,0

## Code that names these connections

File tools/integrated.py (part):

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    ("VDD3P3_RTC","XTAL_32K_P","XTAL_32K_N"),20)})
S3_LABELS.update({str(i):n for i,n in enumerate(
    ("SPICS1","VDD_SPI","SPIHD","SPIWP","SPICS0","SPICLK","SPIQ","SPID","SPICLK_N","SPICLK_P"),28)})
S3_LABELS.update({"46":"VDD3P3_CPU","53":"XTAL_N","54":"XTAL_P","55":"VDDA","56":"VDDA","57":"GND_EP"})
LABELS = {"S3":dict(sorted(S3_LABELS.items(),key=lambda pair:int(pair[0]))),
          "USB_C":{"A5":"CC1","B5":"CC2","A6":"D+","B6":"D+",
                   "A7":"D-","B7":"D-","A8":"SBU1","B8":"SBU2","S1":"SHELL"} |
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    m.update({"1":"RF_CHIP","2":"RF_3V3","3":"RF_3V3","4":"CHIP_EN",
              "20":"V3V3","29":"VDD_SPI","46":"V3V3","53":"XTAL_N","54":"XTAL_P",
              "55":"RF_3V3","56":"RF_3V3","57":"GND",
              str(GPIO[0]):"BOOT0",str(GPIO[19]):"USB_N_MCU",str(GPIO[20]):"USB_P_MCU"})
    usb={n:label for n,label in LABELS["USB_C"].items() if label in ("GND","VBUS","CC1","CC2")}
    usb={n:("VBUS_RAW" if label=="VBUS" else label) for n,label in usb.items()}
    usb.update({"A6":"USB_P","B6":"USB_P","A7":"USB_N","B7":"USB_N","S1":"GND"})
    def part(ref,val,kind,pos,*pins):
        return a.Part(ref,val,kind,pos,a.pn(*pins))
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        part("TP1","BOOT","Probe",(59,3.4),"BOOT0"),
        part("TP2","RESET","Probe",(57,2),"CHIP_EN"),
        part("TP3","GND","Probe",(48,3),"GND"),
        part("TP4","UART_RX","Probe",(51,3),"LED_GPIO"),
        part("TP5","UART_TX","Probe",(54,3),"PDM_DATA_MCU"),
        part("X1","40 MHz / 10 pF","Xtal",(48.2,6.4),"XTAL_P","GND","XTAL_N","GND"),
        part("C17","15p C0G tune","C0603",(44.4,6.3),"XTAL_P","GND"),
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
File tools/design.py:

"""Shared Rev A4 placement, pins and netlist. Units: mm; XY from PCB top left."""
from dataclasses import dataclass
from pathlib import Path

ROOT = Path(__file__).resolve().parents[1]
W, H = 95, 98
MOUNT = [(4, 4), (91, 4), (4, 94), (91, 94)]
XS = [18.4 + 19.05*i for i in range(4)]
YS = [33.30 + 19.05*i for i in range(4)]
TOUCH, JOY = (XS[0],YS[3]), (XS[3],YS[0])
ENC = (XS[0], YS[0])
MCU = ((XS[1]+XS[2])/2, 0.25)
MIC = (13,11)
MIC_PORT_OFFSET = (0,-.78)  # ST DS12698 Fig. 11, rotated to match Fig. 12
MIC_PORT = tuple(a+b for a,b in zip(MIC,MIC_PORT_OFFSET))
MIC_BORE = 1.6
MIC_BOSS_Z = 8.0
MIC_CLK, MIC_DATA = 3,43
NAMES = ('SLOT1 SLOT2 NEW_CHAT PTT SLOT3 SLOT4 ACCEPT DECLINE '
         'SLOT5 SLOT6 FIND INTERRUPT PTT_B DIAL_PUSH '
         'JOY_UP JOY_RIGHT JOY_DOWN JOY_LEFT JOY_CENTER').split()
MATRIX = [[0,1,2,3,4], [5,6,7,8,9], [10,11,12,13,-1], [14,15,16,17,18]]
ROWS, COLS = [5,6,7,8], [9,10,11,12,13]
ENC_PINS, TOUCH_PIN, LED_PIN = (1,2), 4, 44
KEY_GRID = [(1,0),(2,0),(0,2),(1,3),(0,1),(1,1),(1,2),
            (2,2),(2,1),(3,1),(3,3),(3,2),(2,3)]
KEYS = [(XS[x],YS[y]) for x,y in KEY_GRID]
LED_KEYS = [0,1,4,5,8,9]
PTT_PRIMARY, PTT_SECONDARY = 3,12
LEDS = [(KEYS[i][0]+(-5.1 if i==0 else 5.1 if i==1 else 0), KEYS[i][1]-9.525) for i in LED_KEYS]

@dataclass
class Part:
    ref: str
    val: str
    kind: str
    xy: tuple
    nets: dict

parts = []
def add(ref,val,kind,xy,**nets):
    parts.append(Part(ref,val,kind,xy,nets))

def pn(*nets):
    return {str(i+1): n for i,n in enumerate(nets)}

m = {'5V':'VBUS','GND':'GND','3V3':'V3V3','1':'ENC_A','2':'ENC_B',
     str(TOUCH_PIN):'TOUCH_MCU',str(LED_PIN):'LED_GPIO',
     str(MIC_CLK):'PDM_CLK_MCU',str(MIC_DATA):'PDM_DATA_MCU'}
m.update({str(pin):f'ROW{i}' for i,pin in enumerate(ROWS)})
m.update({str(pin):f'COL{i}' for i,pin in enumerate(COLS)})
add('U1','ESP32-S3-Zero-M','Zero',MCU,**m)

for row, line in enumerate(MATRIX):
    for col, i in enumerate(line):
        if i < 0:
            continue
        colnet, rownet = f'COL{col}', f'ROW{row}'
        if i < 13:
            x,y = KEYS[i]
            add(f'SW{i+1}',NAMES[i],'MX',(x,y),**pn(colnet,f'K{i+1}'))
            dxy = (x+9.525,y+5.2)
        elif i == 13:
            add('SW14','EC11E15244G1','EC11',ENC,
                **{'A':'ENC_A','B':'ENC_B','C':'GND','S1':colnet,'S2':'K14','MP':'GND'})
            dxy = (ENC[0]+1,ENC[1]-12.8)
        else:
            dxy = (JOY[0]-9.5+(i-14)*4.75,JOY[1]-17.8)
        # Active row low; column input pull-up. K/cathode on pin 1.
        add(f'D{i+1}','BAT46W-7-F','SOD123',dxy,**pn(rownet,f'K{i+1}'))

# Rotating the printed cap 45 degrees marks the physical diagonal directions.
# Drawing #1 terminal names A,B,C,D map to up,right,left,down in firmware.
# Common is on the columns' diode side; wire these diodes anode to column,
# cathode to direction, so the shared joystick common can be driven ROW3.
for i, p in enumerate(parts):
    if p.ref in [f'D{j}' for j in range(15,20)]:
        j = int(p.ref[1:])-15
        parts[i] = Part(p.ref,p.val,p.kind,p.xy,pn(f'K{j+15}',f'COL{j}'))
add('SW15','SKRHAAE010','SKRH',JOY,**pn('K15','K19','K18','K16','ROW3','K17'))

add('U2','SN74LV1T125DBVR','SOT23_5',(24,11),**pn('GND','LED_GPIO','GND','LED_BUF','LED_5V'))
add('U3','TPS22918DBVR','SOT23_6',(32,9),**pn('VBUS','GND','V3V3','LED_CT',None,'LED_5V'))
add('R1','330R','R0603',(24,15),**pn('LED_BUF','PIX0'))
add('R2','1k','R0603',(12,84),**pn('TOUCH_MCU','TOUCH_FOIL'))
for i in range(5):
    add(f'R{i+3}','22k','R0603',(66+i*4.6,10.4),**pn('V3V3',f'COL{i}'))
add('J1','Touch foil wire','Wire',TOUCH,**pn('TOUCH_FOIL'))
for i,(x,y) in enumerate(LEDS):
    add(f'LED{i+1}','WS2812B-MINI-V6','RGB3535',(x,y),**pn('LED_5V',f'PIX{i+1}' if i<5 else None,'GND',f'PIX{i}'))
    add(f'C{i+1}','100n','C0603',(x+(-4.6 if i==0 else 4.6),y-3.6 if i<2 else y+1.4),**pn('LED_5V','GND'))
add('C7','100n','C0603',(28,10),**pn('LED_5V','GND'))
add('C8','47u 10V','C1206',(32,16.0),**pn('LED_5V','GND'))
add('C9','4.7n C0G','C0603',(32,4.5),**pn('LED_CT','GND'))
add('C10','1u 16V','C0603',(36.4,8.5),**pn('VBUS','GND'))
add('U4','MP34DT06JTR','MP34DT06J',MIC,**pn('V3V3','GND','PDM_CLK','PDM_DATA','GND'))
add('C11','100n','C0603',(17.0,11.7),**pn('V3V3','GND'))
add('C12','1u 16V','C0603',(17.0,14.0),**pn('V3V3','GND'))
add('R8','33R','R0603',(35.8,18.0),**pn('PDM_CLK','PDM_CLK_MCU'))
add('R9','470R','R0603',(59,2.2),**pn('PDM_DATA_MCU','PDM_DATA'))
for i, xy in enumerate(MOUNT,1):
    add(f'H{i}','M2','Mount',xy)

BOM = [
    ('U1',1,'Waveshare ESP32-S3-Zero-M (4 MB / 2 MB)','with 2x9 male headers',19,28),
    ('U2',1,'TI SN74LV1T125DBVR','SOT-23-5; 1.8–5.5 V translator',0.7,2.5),
    ('U3',1,'TI TPS22918DBVR','SOT-23-6; 5 V LED rail load switch',1.5,5),
    ('SW1-SW13',13,'MX-compatible 3-pin or 5-pin switches','solder type; match SW4 and SW13 for the shared 2U cap',0.65,1.5),
    ('SW14',1,'ALPS EC11E15244G1','push encoder; confirm drawing / D shaft',5,12),
    ('SW15',1,'ALPS SKRHAAE010','no guide bosses; verify footprint before substituting',5,16),
    ('D1-D19',19,'Diodes Inc. BAT46W-7-F','SOD-123; low forward drop Schottky',0.08,0.30),
    ('LED1-LED6',6,'Worldsemi WS2812B-MINI-V6','3535; verify MINI-V6 (no X1 suffix)',0.3,0.9),
    ('R1',1,'330 ohm','0603',0.02,0.1),
    ('R2',1,'1 kohm','0603',0.02,0.1),
    ('R3-R7',5,'22 kohm ±1%','0603; matrix column pull-ups',0.02,0.1),
    ('C1-C7',7,'100 nF X7R 16 V','0603',0.04,0.12),
    ('C8',1,'47 uF X5R 10 V','1206; ceramic',0.3,1),
    ('C9',1,'4.7 nF C0G 50 V','0603; load-switch slew-rate capacitor',0.04,0.2),
    ('C10',1,'1 uF X7R 16 V','0603; load-switch input bypass',0.05,0.2),
    ('U4',1,'ST MP34DT06JTR','C503097; top-port PDM; no wash or coating over inlet',3,9),
    ('C11',1,'100 nF X7R 16 V','0603; microphone bypass',0.04,0.12),
    ('C12',1,'1 uF X7R 16 V','0603; microphone bypass',0.05,0.2),
    ('R8',1,'33 ohm','0603; source series resistor on PDM clock',0.02,0.1),
    ('R9',1,'470 ohm','0603; limits contention at GPIO43 during reset',0.02,0.1),
    ('MIC-SEAL',1,'0.8 mm closed-cell foam, ID 1.6 mm / OD 2.8 mm','ring on underside of plate; keep inlet clear',0.1,0.5),
    ('PCB',1,'2-layer FR4 1.6 mm','95 x 98 mm; bare PCB; per board in small batch',5,20),
    ('CAPS-A',6,'MX 1U frosted translucent keycaps','matte clear or milky PC; 17.9 mm reference width',0.7,2.5),
    ('CAPS-C',5,'MX 1U opaque command caps','add optional icon decals',0.35,1.2),
    ('PRINT',1,'PLA/PETG + translucent material','base, plate, knobs, light pipes and dual-stem 2U cap',4.5,11),
    ('SCREWS',4,'M2x10 pan-head screws','self-tap into printed pilot holes',0.1,0.35),
    ('FOIL',1,'Copper adhesive foil + thin wire','14 mm square + 50 mm wire',0.2,1),
    ('USB',1,'USB-C data cable','reuse an existing cable',0,8),
]
